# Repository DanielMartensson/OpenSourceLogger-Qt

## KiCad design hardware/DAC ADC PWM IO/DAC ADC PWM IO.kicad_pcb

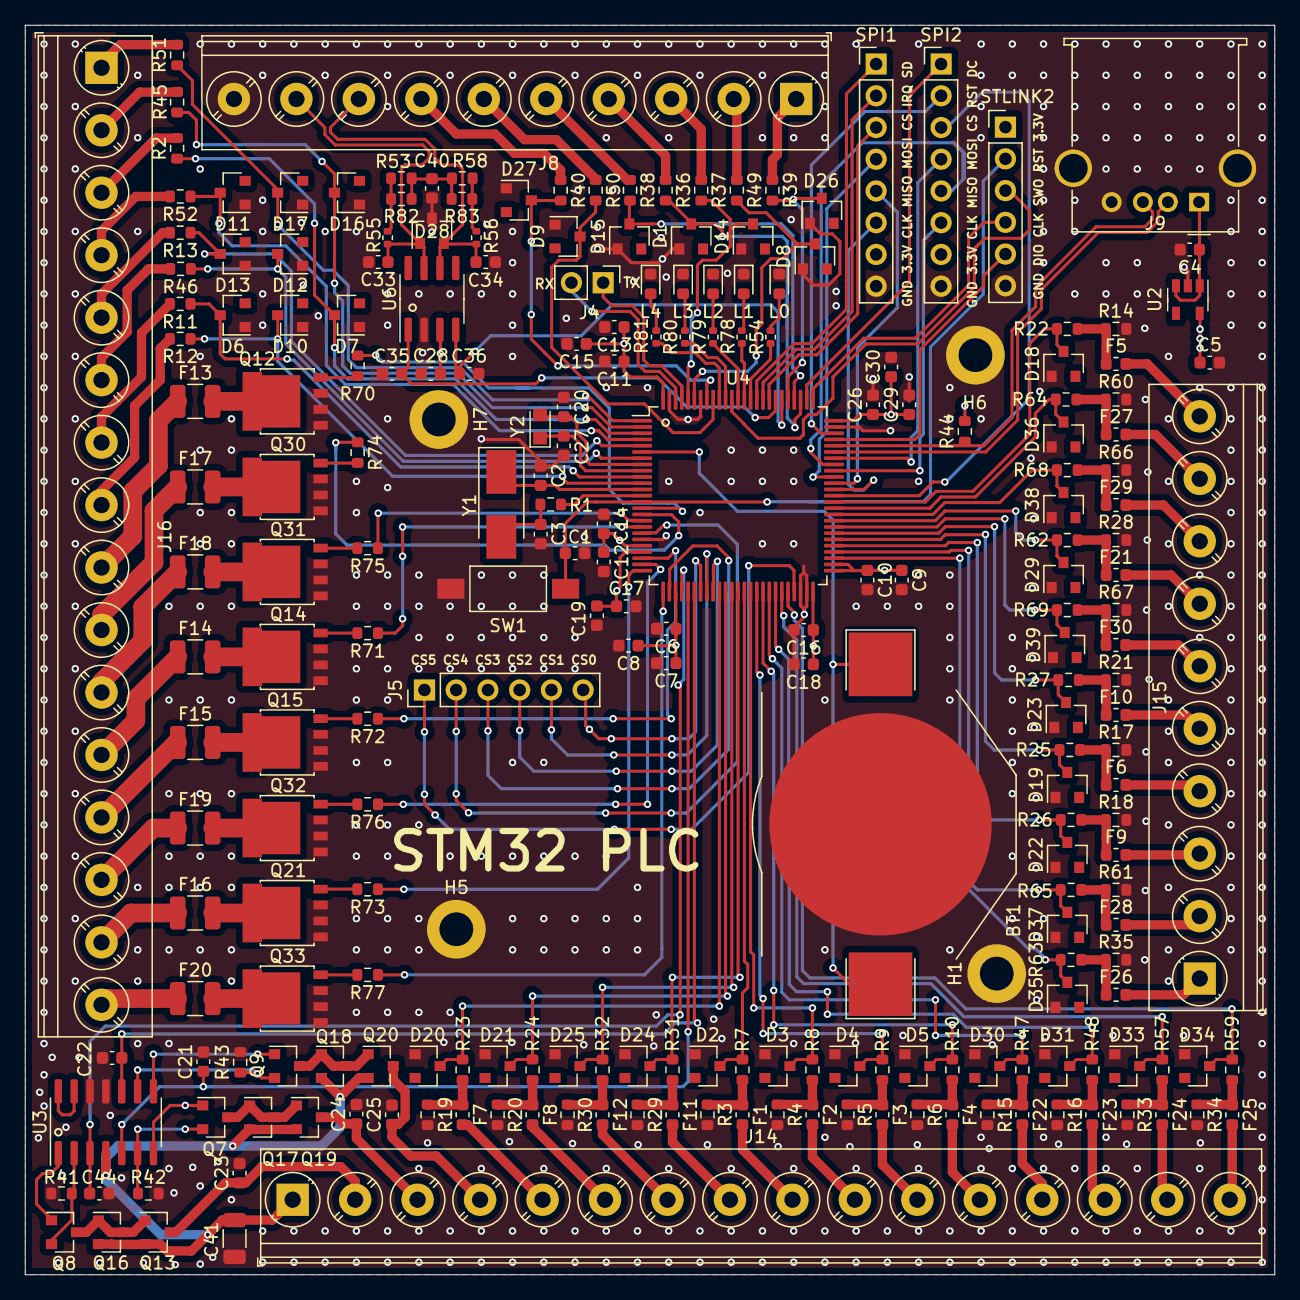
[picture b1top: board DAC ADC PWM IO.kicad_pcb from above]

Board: 4 copper layers, 100.0 x 100.0 mm, 232 parts (0 on the bottom side), 197 nets.

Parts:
BT1: Battery_Cell; BatteryHolder_Keystone_3002_1x2032
C1, C6, C7, C11, C13, C26, C29: 100nF; C_0603_1608Metric
C2, C3, C20, C27: 15pF; C_0603_1608Metric
C4, C5, C9, C14, C18, C19: 1uF; C_0603_1608Metric
C8, C15, C30: 4.7uF; C_0603_1608Metric
C10, C12, C16, C17, C21, C22, C23, C24, C25, C28, C33, C34, C35, C36, C40, C44: 10nF; C_0603_1608Metric
C41: 10uF; C_1206_3216Metric
D1, D2, D3, D4, D5, D6, D7, D8, D9, D10, D11, D12, D13, D14, D15, D16, D17, D18, D19, D20, D21, D22, D23, D24, D25, D26, D27, D29, D30, D31, D33, D34, D35, D36, D37, D38, D39: BZX84C3V6LT1G; D_SOT-23_ANK
D28: PESD5V0L2BT,215; SOT-23
F1, F2, F3, F4, F5, F6, F7, F8, F9, F10, F11, F12, F21, F22, F23, F24, F25, F26, F27, F28, F29, F30: Max 120mA; Fuse_0603_1608Metric
F13, F14, F15, F16, F17, F18, F19, F20: Max 2.2A; Fuse_1210_3225Metric
H1, H5, H6, H7: MountingHole_Pad; MountingHole_2.7mm_M2.5_DIN965_Pad
J4: Conn_01x02; PinHeader_1x02_P2.54mm_Vertical
J5: Chip Select; PinHeader_1x06_P2.54mm_Vertical
J8, J15: Screw_Terminal_01x10; TerminalBlock_Phoenix_PT-1,5-10-5.0-H_1x10_P5.00mm_Horizont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
J9: USB_A; USB_A_Molex_67643_Horizontal
J14, J16: Screw_Terminal_01x16; TerminalBlock_Phoenix_PT-1,5-16-5.0-H_1x16_P5.00mm_Horizont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
L0, L1, L2, L3, L4: LED; LED_0603_1608Metric
Q7, Q8, Q9: MMBT5551; SOT-23
Q12, Q14, Q15, Q21, Q30, Q31, Q32, Q33: PSMN025-80YL; LFPAK56
Q13, Q16, Q17, Q18, Q19, Q20: MMBT5401; SOT-23
R1, R44: 1.5k; R_0603_1608Metric
R2, R7, R8, R9, R10, R11, R12, R13, R22, R23, R24, R25, R26, R27, R31, R32, R36, R37, R38, R39, R40, R45, R46, R47, R48, R49, R50, R51, R52, R57, R59, R62, R63, R64, R65, R68, R69: 10k; R_0603_1608Metric
R3, R4, R5, R6, R14, R15, R16, R17, R18, R19, R20, R21, R28, R29, R30, R33, R34, R35, R41, R42, R43, R60, R61, R66, R67, R70, R71, R72, R73, R74, R75, R76, R77: 160; R_0603_1608Metric
R53, R58, R82, R83: 120; R_0603_1608Metric
R54, R78, R79, R80, R81: 220; R_0402_1005Metric
R55, R56: 0; R_0402_1005Metric
SPI1, SPI2: Conn_01x08; PinHeader_1x08_P2.54mm_Vertical
STLINK2: ST-Link V2 connetor; PinHeader_1x06_P2.54mm_Vertical
SW1: SW_Push; SW_SPST_FSMSM
U2: AP7365-33WG-7; SOT-23-5
U3: MC33079DT; SO-14_3.9x8.65mm_P1.27mm
U4: STM32F373VBTx; LQFP-100_14x14mm_P0.5mm
U6: TCAN332; SOIC-8_3.9x4.9mm_P1.27mm
Y1: HSE; Crystal_SMD_5032-2Pin_5.0x3.2mm_HandSoldering
Y2: 32.768 kHz; Crystal_SMD_2012-2Pin_2.0x1.2mm_HandSoldering

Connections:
+3V3: C5.1, C6.1, C7.1, C8.1, C9.1, C10.1, C11.1, C12.1, C13.1, C14.1, C15.1, C16.1, C17.1, C18.1, C19.1, C26.1, C28.1, C29.1, C30.1, R44.2, SPI1.7, SPI2.7, STLINK2.1, U2.5, U4.21, U4.22, U4.28, U4.50, U4.51, U4.52, U4.75, U4.100, U6.3
+5V: C4.1, J9.1, U2.1, U2.3
/CAN/CAN+: C33.2, D28.1, J8.9, R55.1, U6.7
/CAN/CAN-: C34.1, D28.2, J8.8, R56.2, U6.6
/DAC/AO0: C23.1, J14.2, Q13.3
/DAC/AO1: C24.1, J14.3, Q19.3
/DAC/AO2: C25.1, J14.4, Q20.3
/DAC/VDC: C41.1, J14.1, Q13.2, Q16.2, Q17.2, Q18.2, Q19.2, Q20.2, U3.4
/DSDADC/DAI0M: F28.2, J15.2
/DSDADC/DAI0P: F26.2, J15.1
/DSDADC/DAI1M: F6.2, J15.4
/DSDADC/DAI1P: F9.2, J15.3
/DSDADC/DAI2M: F30.2, J15.6
/DSDADC/DAI2P: F10.2, J15.5
/DSDADC/DAI3M: F29.2, J15.8
/DSDADC/DAI3P: F21.2, J15.7
/DSDADC/DAI4M: F5.2, J15.10
/DSDADC/DAI4P: F27.2, J15.9
/Digital/P0: F13.1, J16.9
/Digital/P1: F17.1, J16.10
/Digital/P2: F18.1, J16.11
/Digital/P3: F14.1, J16.12
/Digital/P4: F15.1, J16.13
/Digital/P5: F19.1, J16.14
/Digital/P6: F16.1, J16.15
/Digital/P7: F20.1, J16.16
/INPUT/DI0: J16.1, R51.2
/INPUT/DI1: J16.2, R45.1
/INPUT/DI2: J16.3, R2.2
/INPUT/DI3: J16.4, R52.2
/INPUT/DI4: J16.5, R13.2
/INPUT/DI5: J16.6, R46.2
/INPUT/DI6: J16.7, R11.2
/INPUT/DI7: J16.8, R12.1
/Pulse/E0+: J8.7, R40.1
/Pulse/E0-: J8.6, R50.1
/Pulse/E1+: J8.5, R38.1
/Pulse/E1-: J8.4, R36.1
/Pulse/FI0: J8.3, R37.1
/Pulse/FI1: J8.2, R49.1
/Pulse/FI2: J8.1, R39.1
/SDADC/AI0: F7.2, J14.5
/SDADC/AI1: F8.2, J14.6
/SDADC/AI2: F12.2, J14.7
/SDADC/AI3: F11.2, J14.8
/SDADC/AI4: F1.2, J14.9
/SDADC/AI5: F2.2, J14.10
/SDADC/AI6: F3.2, J14.11
/SDADC/AI7: F4.2, J14.12
/SDADC/AI8: F22.2, J14.13
/SDADC/AI9: F23.2, J14.14
/SDADC/AI10: F24.2, J14.15
/SDADC/AI11: F25.2, J14.16
GND: BT1.2, C1.1, C2.1, C3.1, C4.2, C5.2, C6.2, C7.2, C8.2, C9.2, C10.2, C11.2, C12.2, C13.2, C14.2, C15.2, C16.2, C17.2, C18.2, C19.2, C20.1, C21.2, C22.2, C23.2, C24.2, C25.2, C26.2, C27.1, C28.2, C29.2, C30.2, C33.1, C34.2, C35.1, C36.2, C40.2, C41.2, C44.2, D1.2, D2.2, D3.2, D4.2, D5.2, D6.2, D7.2, D8.2, D9.2, D10.2, D11.2, D12.2, D13.2, D14.2, D15.2, D16.2, D17.2, D18.2, D19.2, D20.2, D21.2, D22.2, D23.2, D24.2, D25.2, D26.2, D27.2, D28.3, D29.2, D30.2, D31.2, D33.2, D34.2, D35.2, D36.2, D37.2, D38.2, D39.2, H1.1, H5.1, H6.1, H7.1, J8.10, J9.4, J9.5, L0.1, L1.1, L2.1, L3.1, L4.1, Q12.1, Q12.2, Q12.3, Q14.1, Q14.2, Q14.3, Q15.1, Q15.2, Q15.3, Q21.1, Q21.2, Q21.3, Q30.1, Q30.2, Q30.3, Q31.1, Q31.2, Q31.3, Q32.1, Q32.2, Q32.3, Q33.1, Q33.2, Q33.3, R3.2, R4.2, R5.2, R6.2, R14.2, R15.2, R16.2, R17.2, R18.2, R19.2, R20.2, R21.2, R28.2, R29.2, R30.2, R33.2, R34.2, R35.2, R41.2, R42.2, R43.2, R60.2, R61.2, R66.2, R67.2, SPI1.8, SPI2.8, STLINK2.6, SW1.1, U2.2, U3.11, U3.12, U4.20, U4.48, U4.49, U4.74, U4.94, U4.99, U6.2
NRST: C1.2, STLINK2.2, SW1.2, U4.14
unnamed: BT1.1, U4.6
unnamed: C3.2, R1.1, Y1.2
unnamed: C40.1, R53.2, R58.1, R82.2, R83.1
unnamed: F1.1, R3.1, R7.1
unnamed: F2.1, R4.1, R8.1
unnamed: F3.1, R5.1, R9.1
unnamed: F4.1, R6.1, R10.1
unnamed: F5.1, R14.1, R22.1
unnamed: F6.1, R17.1, R25.1
unnamed: F7.1, R19.1, R23.1
unnamed: F8.1, R20.1, R24.1
unnamed: F9.1, R18.1, R26.1
unnamed: F10.1, R21.1, R27.1
unnamed: F11.1, R29.1, R31.1
unnamed: F12.1, R30.1, R32.1
unnamed: F13.2, Q12.5
unnamed: F14.2, Q14.5
unnamed: F15.2, Q15.5
unnamed: F16.2, Q21.5
unnamed: F17.2, Q30.5
unnamed: F18.2, Q31.5
unnamed: F19.2, Q32.5
unnamed: F20.2, Q33.5
unnamed: F21.1, R28.1, R62.1
unnamed: F22.1, R15.1, R47.1
unnamed: F23.1, R16.1, R48.1
unnamed: F24.1, R33.1, R57.1
unnamed: F25.1, R34.1, R59.1
unnamed: F26.1, R35.1, R63.1
unnamed: F27.1, R60.1, R64.1
unnamed: F28.1, R61.1, R65.1
unnamed: F29.1, R66.1, R68.1
unnamed: F30.1, R67.1, R69.1
unnamed: L0.2, R54.2
unnamed: L1.2, R78.2
unnamed: L2.2, R79.2
unnamed: L3.2, R80.2
unnamed: L4.2, R81.2
unnamed: Q7.1, U3.7
unnamed: Q7.2, R42.1, U3.6
unnamed: Q8.1, U3.1
unnamed: Q8.2, R41.1, U3.2
unnamed: Q9.1, U3.8
unnamed: Q9.2, R43.1, U3.9
unnamed: Q12.4, R70.2
unnamed: Q8.3, Q13.1, Q16.1, Q16.3
unnamed: Q14.4, R71.2
unnamed: Q15.4, R72.2
unnamed: Q7.3, Q17.1, Q17.3, Q19.1
unnamed: Q9.3, Q18.1, Q18.3, Q20.1
unnamed: Q21.4, R73.2
unnamed: Q30.4, R74.2
unnamed: Q31.4, R75.2
unnamed: Q32.4, R76.2
unnamed: Q33.4, R77.2
unnamed: R53.1, R55.2, R82.1
unnamed: R56.1, R58.2, R83.2
unnamed: U3.13, U3.14
PA0: R72.1, U4.23
PA1: R76.1, U4.24
PA2: R73.1, U4.25
PA3: R77.1, U4.26
PA4: C44.1, U3.3, U4.29
PA5: C21.1, U3.5, U4.30
PA6: C22.1, U3.10, U4.31
PA7: J5.6, U4.32
PA8: SPI2.6, U4.67
PA9: SPI2.5, U4.68
PA10: SPI2.4, U4.69
PA13: STLINK2.5, U4.72
PA14: STLINK2.4, U4.76
PA15: SPI2.1, U4.77
PB0: D20.1, R23.2, U4.35
PB1: D21.1, R24.2, U4.36
PB2: D25.1, R32.2, U4.37
PB3: STLINK2.3, U4.89
PB4: R80.1, U4.90
PB5: R81.1, U4.91
PB6: D9.1, R50.2, U4.92
PB7: D27.1, R40.2, U4.93
PB8: D8.1, R49.2, U4.95
PB9: D14.1, R37.2, U4.96
PB10: J5.1, U4.47
PB14: D35.1, R63.2, U4.53
PB15: D37.1, R65.2, U4.54
PC0: R70.1, U4.15
PC1: R74.1, U4.16
PC2: R75.1, U4.17
PC3: R71.1, U4.18
PC4: J5.5, U4.33
PC5: J5.4, U4.34
PC6: SPI2.3, U4.63
PC7: SPI1.6, U4.64
PC8: SPI1.5, U4.65
PC9: SPI1.4, U4.66
PC10: D1.1, R36.2, U4.78
PC11: D15.1, R38.2, U4.79
PC12: D26.1, R39.2, U4.80
PC13: D12.1, R46.1, U4.7
PC14: C20.2, U4.8, Y2.2
PC15: C27.2, U4.9, Y2.1
PD0: C36.1, U4.81, U6.4
PD1: C35.2, U4.82, U6.1
PD2: SPI1.3, U4.83
PD3: SPI1.2, U4.84
PD4: SPI1.1, U4.85
PD5: R54.1, U4.86
PD6: R78.1, U4.87
PD7: R79.1, U4.88
PD8: D22.1, R26.2, U4.55
PD9: D19.1, R25.2, U4.56
PD10: D23.1, R27.2, U4.57
PD11: D39.1, R69.2, U4.58
PD12: D29.1, R62.2, U4.59
PD13: D38.1, R68.2, U4.60
PD14: D36.1, R64.2, U4.61
PD15: D18.1, R22.2, U4.62
PE0: J4.1, U4.97
PE1: J4.2, U4.98
PE2: D17.1, R51.1, U4.1
PE3: D16.1, R45.2, U4.2
PE4: D7.1, R2.1, U4.3
PE5: D11.1, R52.1, U4.4
PE6: D13.1, R13.1, U4.5
PE7: D24.1, R31.2, U4.38
PE8: D2.1, R7.2, U4.39
PE9: D3.1, R8.2, U4.40
PE10: D4.1, R9.2, U4.41
PE11: D5.1, R10.2, U4.42
PE12: D30.1, R47.2, U4.43
PE13: D31.1, R48.2, U4.44
PE14: D33.1, R57.2, U4.45
PE15: D34.1, R59.2, U4.46
PF0: C2.2, U4.12, Y1.1
PF1: R1.2, U4.13
PF2: J5.2, U4.19
PF4: J5.3, U4.27
PF6: SPI2.2, U4.73
PF9: D6.1, R11.1, U4.10
PF10: D10.1, R12.2, U4.11
USB+: J9.3, R44.1, U4.71
USB-: J9.2, U4.70

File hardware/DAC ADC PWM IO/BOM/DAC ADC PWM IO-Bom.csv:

Comment,Designator,Footprint,LCSC
10nF,"C10,C12,C16,C17,C21,C22,C23,C24,C25,C28,C33,C34,C35,C36,C40,C44",Capacitor_SMD:C_0603_1608Metric,C57112
15pF,"C2,C3,C20,C27",Capacitor_SMD:C_0603_1608Metric,C1644
1uF,"C4,C5,C9,C14,C18,C19",Capacitor_SMD:C_0603_1608Metric,C15849
100nF,"C1,C6,C7,C11,C13,C26,C29",Capacitor_SMD:C_0603_1608Metric,C14663
4.7uF,"C8,C15,C30",Capacitor_SMD:C_0603_1608Metric,C19666
BZX84C3V6LT1G,"D1,D2,D3,D4,D5,D6,D7,D8,D9,D10,D11,D12,D13,D14,D15,D16,D17,D18,D19,D20,D21,D22,D23,D24,D25,D26,D27,D29,D30,D31,D33,D34,D35,D36,D37,D38,D39",Diode_SMD:D_SOT-23_ANK,C118564
Max 120mA,"F1,F2,F3,F4,F5,F6,F7,F8,F9,F10,F11,F12,F21,F22,F23,F24,F25,F26,F27,F28,F29,F30",Fuse:Fuse_0603_1608Metric,C426238
Max 2.2A,"F13,F14,F15,F16,F17,F18,F19,F20",Fuse:Fuse_1210_3225Metric,C20992
LED,"L0,L1,L2,L3,L4",LED_SMD:LED_0603_1608Metric,C2286
MMBT5401,"Q13,Q16,Q17,Q18,Q19,Q20",Package_TO_SOT_SMD:SOT-23,C8326
MMBT5551,"Q7,Q8,Q9",Package_TO_SOT_SMD:SOT-23,C2145
1.5k,"R1,R44",Resistor_SMD:R_0603_1608Metric,C22843
10k,"R2,R7,R8,R9,R10,R11,R12,R13,R22,R23,R24,R25,R26,R27,R31,R32,R36,R37,R38,R39,R40,R45,R46,R47,R48,R49,R50,R51,R52,R57,R59,R62,R63,R64,R65,R68,R69",Resistor_SMD:R_0603_1608Metric,C25804
220,"R54,R78,R79,R80,R81",Resistor_SMD:R_0402_1005Metric,C25091
120,"R53,R58,R82,R83",Resistor_SMD:R_0603_1608Metric,C22787
160,"R3,R4,R5,R6,R14,R15,R16,R17,R18,R19,R20,R21,R28,R29,R30,R33,R34,R35,R41,R42,R43,R60,R61,R66,R67,R70,R71,R72,R73,R74,R75,R76,R77",Resistor_SMD:R_0603_1608Metric,C22814

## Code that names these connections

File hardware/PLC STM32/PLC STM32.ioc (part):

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Mcu.Name=STM32F373V(8-B-C)Tx
Mcu.Package=LQFP100
Mcu.UserName=STM32F373VBTx
PA0.GPIOParameters=GPIO_Label
PA0.GPIO_Label=PWM4
PA0.Signal=S_TIM2_CH1_ETR
PA1.GPIOParameters=GPIO_Label
PA1.GPIO_Label=PWM5
PA1.Signal=S_TIM2_CH2
PA11.Mode=Device
PA11.Signal=USB_DM
PA12.Mode=Device
PA12.Signal=USB_DP
PA13.Mode=Trace_Asynchronous_SW
PA13.Signal=SYS_JTMS-SWDIO
PA14.Mode=Trace_Asynchronous_SW
PA14.Signal=SYS_JTCK-SWCLK
PA2.GPIOParameters=GPIO_Label
PA2.GPIO_Label=PWM6
PA2.Signal=S_TIM2_CH3
PA3.GPIOParameters=GPIO_Label
PA3.GPIO_Label=PWM7
PA3.Signal=S_TIM2_CH4
PA4.GPIOParameters=GPIO_Label
PA4.GPIO_Label=AO0
PA4.Signal=COMP_DAC11_group
PA5.GPIOParameters=GPIO_Label
PA5.GPIO_Label=AO1
PA5.Signal=COMP_DAC12_group
PA6.GPIOParameters=GPIO_Label
PA6.GPIO_Label=AO2
PA6.Signal=COMP_DAC21_group
PB0.GPIOParameters=GPIO_Label
PB0.GPIO_Label=AI0
PB0.Mode=IN6-Single-Ended zero reference
PB0.Signal=SDADC1_AIN6P
PB1.GPIOParameters=GPIO_Label
PB1.GPIO_Label=AI1
PB1.Mode=IN5-Single-Ended zero reference
PB1.Signal=SDADC1_AIN5P
PB14.GPIOParameters=GPIO_Label
PB14.GPIO_Label=DAI0P
PB14.Mode=IN8-Differential
PB14.Signal=SDADC3_AIN8P
PB15.GPIOParameters=GPIO_Label
PB15.GPIO_Label=DAI0M
PB15.Mode=IN8-Differential
PB15.Signal=SDADC3_AIN8M
PB2.GPIOParameters=GPIO_Label
PB2.GPIO_Label=AI2
PB2.Mode=IN4-Single-Ended zero reference
PB2.Signal=SDADC1_AIN4P
PB3.Mode=Trace_Asynchronous_SW
PB3.Signal=SYS_JTDO-TRACESWO
PB4.GPIOParameters=GPIO_Label
PB4.GPIO_Label=LED3
PB4.Signal=GPIO_Output
PB5.GPIOParameters=GPIO_Label
PB5.GPIO_Label=LED4
PB5.Signal=GPIO_Output
PB6.GPIOParameters=GPIO_Label
PB6.GPIO_Label=E0-
PB6.Signal=S_TIM4_CH1
PB7.GPIOParameters=GPIO_Label
PB7.GPIO_Label=E0+
PB7.Signal=S_TIM4_CH2
PB8.GPIOParameters=GPIO_Label
PB8.GPIO_Label=IC1
PB8.Signal=S_TIM16_CH1
PB9.GPIOParameters=GPIO_Label
PB9.GPIO_Label=IC0
PB9.Signal=S_TIM17_CH1
PC0.GPIOParameters=GPIO_Label
PC0.GPIO_Label=PWM0
PC0.Signal=S_TIM5_CH1_ETR
PC1.GPIOParameters=GPIO_Label
PC1.GPIO_Label=PWM1
PC1.Signal=S_TIM5_CH2
PC10.GPIOParameters=GPIO_Label
PC10.GPIO_Label=E1-
PC10.Signal=S_TIM19_CH1
PC11.GPIOParameters=GPIO_Label
PC11.GPIO_Label=E1+
PC11.Signal=S_TIM19_CH2
PC12.GPIOParameters=GPIO_PuPd,GPIO_Label
PC12.GPIO_Label=DI8
PC12.GPIO_PuPd=GPIO_PULLDOWN
PC12.Signal=GPIO_Input
PC13.GPIOParameters=GPIO_PuPd,GPIO_Label
PC13.GPIO_Label=DI5
PC13.GPIO_PuPd=GPIO_PULLDOWN
PC13.Signal=GPIO_Input
PC2.GPIOParameters=GPIO_Label
PC2.GPIO_Label=PWM2
PC2.Signal=S_TIM5_CH3
PC3.GPIOParameters=GPIO_Label
PC3.GPIO_Label=PWM3
PC3.Signal=S_TIM5_CH4
PD0.Mode=CAN_Activate
PD0.Signal=CAN_RX
PD1.Mode=CAN_Activate
PD1.Signal=CAN_TX
PD10.GPIOParameters=GPIO_Label
PD10.GPIO_Label=DAI2P
PD10.Mode=IN4-Differential
PD10.Signal=SDADC3_AIN4P
PD11.GPIOParameters=GPIO_Label
PD11.GPIO_Label=DAI2M
PD11.Mode=IN4-Differential
PD11.Signal=SDADC3_AIN4M
PD12.GPIOParameters=GPIO_Label
PD12.GPIO_Label=DAI3P
PD12.Mode=IN2-Differential
PD12.Signal=SDADC3_AIN2P
PD13.GPIOParameters=GPIO_Label
PD13.GPIO_Label=DAI3M
PD13.Mode=IN2-Differential
PD13.Signal=SDADC3_AIN2M
PD14.GPIOParameters=GPIO_Label
PD14.GPIO_Label=DAI4P
PD14.Mode=IN0-Differential
PD14.Signal=SDADC3_AIN0P
PD15.GPIOParameters=GPIO_Label
PD15.GPIO_Label=DAI4M
PD15.Mode=IN0-Differential
PD15.Signal=SDADC3_AIN0M
PD5.GPIOParameters=GPIO_Label
PD5.GPIO_Label=LED0
PD5.Signal=GPIO_Output
PD6.GPIOParameters=GPIO_Label
PD6.GPIO_Label=LED1
PD6.Signal=GPIO_Output
PD7.GPIOParameters=GPIO_Label
PD7.GPIO_Label=LED2
PD7.Signal=GPIO_Output
PD8.GPIOParameters=GPIO_Label
PD8.GPIO_Label=DAI1P
PD8.Mode=IN6-Differential
PD8.Signal=SDADC3_AIN6P
PD9.GPIOParameters=GPIO_Label
PD9.GPIO_Label=DAI1M
PD9.Mode=IN6-Differential
PD9.Signal=SDADC3_AIN6M
PE10.GPIOParameters=GPIO_Label
PE10.GPIO_Label=AI6
PE10.Mode=IN2-Single-Ended zero reference
PE10.Signal=SDADC1_AIN2P
PE11.GPIOParameters=GPIO_Label
PE11.GPIO_Label=AI7
PE11.Mode=IN1-Single-Ended zero reference
PE11.Signal=SDADC1_AIN1P
PE12.GPIOParameters=GPIO_Label
PE12.GPIO_Label=AI8
PE12.Mode=IN0-Single-Ended zero reference
PE12.Signal=SDADC1_AIN0P
PE13.GPIOParameters=GPIO_Label
PE13.GPIO_Label=AI9
PE13.Mode=IN2-Single-Ended zero reference
PE13.Signal=SDADC2_AIN2P
PE14.GPIOParameters=GPIO_Label
PE14.GPIO_Label=AI10
PE14.Mode=IN1-Single-Ended zero reference
PE14.Signal=SDADC2_AIN1P
PE15.GPIOParameters=GPIO_Label
PE15.GPIO_Label=AI11
PE15.Mode=IN0-Single-Ended zero reference
PE15.Signal=SDADC2_AIN0P
PE2.GPIOParameters=GPIO_PuPd,GPIO_Label
PE2.GPIO_Label=DI0
PE2.GPIO_PuPd=GPIO_PULLDOWN
PE2.Signal=GPIO_Input
PE3.GPIOParameters=GPIO_PuPd,GPIO_Label
PE3.GPIO_Label=DI1
PE3.GPIO_PuPd=GPIO_PULLDOWN
PE3.Signal=GPIO_Input
PE4.GPIOParameters=GPIO_PuPd,GPIO_Label
PE4.GPIO_Label=DI2
PE4.GPIO_PuPd=GPIO_PULLDOWN
PE4.Signal=GPIO_Input
PE5.GPIOParameters=GPIO_PuPd,GPIO_Label
PE5.GPIO_Label=DI3
PE5.GPIO_PuPd=GPIO_PULLDOWN
PE5.Signal=GPIO_Input
PE6.GPIOParameters=GPIO_PuPd,GPIO_Label
PE6.GPIO_Label=DI4
PE6.GPIO_PuPd=GPIO_PULLDOWN
PE6.Signal=GPIO_Input
PE7.GPIOParameters=GPIO_Label
PE7.GPIO_Label=AI3
PE7.Mode=IN3-Single-Ended zero reference
PE7.Signal=SDADC1_AIN3P
PE8.GPIOParameters=GPIO_Label
PE8.GPIO_Label=AI4
PE8.Mode=IN8-Single-Ended zero reference
PE8.Signal=SDADC1_AIN8P
PE9.GPIOParameters=GPIO_Label
PE9.GPIO_Label=AI5
PE9.Mode=IN7-Single-Ended zero reference
PE9.Signal=SDADC1_AIN7P
PF0-OSC_IN.Mode=HSE-External-Oscillator
PF0-OSC_IN.Signal=RCC_OSC_IN
PF1-OSC_OUT.Mode=HSE-External-Oscillator
PF1-OSC_OUT.Signal=RCC_OSC_OUT
PF10.GPIOParameters=GPIO_PuPd,GPIO_Label
PF10.GPIO_Label=DI7
PF10.GPIO_PuPd=GPIO_PULLDOWN
PF10.Signal=GPIO_Input
PF9.GPIOParameters=GPIO_PuPd,GPIO_Label
PF9.GPIO_Label=DI6
PF9.GPIO_PuPd=GPIO_PULLDOWN
PF9.Signal=GPIO_Input
RCC.HSEPLLFreq_Value=8000000
RCC.HSE_Timout=100
RCC.HSE_VALUE=8000000
RCC.SYSCLKFreq_VALUE=48000000
RCC.SYSCLKSource=RCC_SYSCLKSOURCE_PLLCLK
board=custom

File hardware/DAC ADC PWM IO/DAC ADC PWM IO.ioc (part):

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Mcu.Name=STM32F373C(8-B-C)Tx
Mcu.Package=LQFP48
Mcu.UserName=STM32F373CCTx
PA0.Mode=IN0
PA0.Signal=ADC1_IN0
PA1.Mode=IN1
PA1.Signal=ADC1_IN1
PA10.GPIOParameters=GPIO_Label
PA10.GPIO_Label=PWM 1
PA10.Signal=S_TIM2_CH4
PA11.Mode=Device
PA11.Signal=USB_DM
PA12.Mode=Device
PA12.Signal=USB_DP
PA13.Mode=Trace_Asynchronous_SW
PA13.Signal=SYS_JTMS-SWDIO
PA14.Mode=Trace_Asynchronous_SW
PA14.Signal=SYS_JTCK-SWCLK
PA15.GPIOParameters=GPIO_Label
PA15.GPIO_Label=PWM 3
PA15.Signal=S_TIM2_CH1_ETR
PA2.Mode=IN2
PA2.Signal=ADC1_IN2
PA3.Mode=IN3
PA3.Signal=ADC1_IN3
PA4.GPIOParameters=GPIO_Label
PA4.GPIO_Label=DAC 2
PA4.Signal=COMP_DAC11_group
PA5.GPIOParameters=GPIO_Label
PA5.GPIO_Label=DAC 1
PA5.Signal=COMP_DAC12_group
PA6.GPIOParameters=GPIO_Label
PA6.GPIO_Label=DAC 0
PA6.Signal=COMP_DAC21_group
PA8.GPIOParameters=GPIO_Label
PA8.GPIO_Label=FREQUENCY 2
PA8.Signal=S_TIM5_CH1_ETR
PA9.GPIOParameters=GPIO_Label
PA9.GPIO_Label=PWM 0
PA9.Signal=S_TIM2_CH3
PB0.GPIOParameters=GPIO_Label
PB0.GPIO_Label=SDA0_M
PB0.Mode=IN6-Differential
PB0.Signal=SDADC1_AIN6P
PB1.GPIOParameters=GPIO_Label
PB1.GPIO_Label=SDA0_P
PB1.Mode=IN6-Differential
PB1.Signal=SDADC1_AIN6M
PB14.GPIOParameters=GPIO_Label
PB14.GPIO_Label=SDADC 1
PB14.Mode=IN8-Single-Ended zero reference
PB14.Signal=SDADC3_AIN8P
PB15.GPIOParameters=GPIO_Label
PB15.GPIO_Label=SDADC 2
PB15.Mode=IN7-Single-Ended zero reference
PB15.Signal=SDADC3_AIN7P
PB2.GPIOParameters=GPIO_Label
PB2.GPIO_Label=SDADC 0
PB2.Mode=IN4-Single-Ended zero reference
PB2.Signal=SDADC1_AIN4P
PB3.Mode=Trace_Asynchronous_SW
PB3.Signal=SYS_JTDO-TRACESWO
PB4.GPIOParameters=GPIO_Label
PB4.GPIO_Label=E-
PB4.Signal=S_TIM3_CH1
PB5.GPIOParameters=GPIO_Label
PB5.GPIO_Label=E+
PB5.Signal=S_TIM3_CH2
PB6.GPIOParameters=GPIO_Label
PB6.GPIO_Label=PWM 4
PB6.Signal=S_TIM4_CH1
PB7.GPIOParameters=GPIO_Label
PB7.GPIO_Label=PWM 5
PB7.Signal=S_TIM4_CH2
PB8.GPIOParameters=GPIO_Label
PB8.GPIO_Label=FREQUENCY 1
PB8.Signal=S_TIM19_CH3
PB9.GPIOParameters=GPIO_Label
PB9.GPIO_Label=FREQUENCY 0
PB9.Signal=S_TIM19_CH4
PC13.GPIOParameters=GPIO_PuPd,GPIO_Label
PC13.GPIO_Label=INPUT 1
PC13.GPIO_PuPd=GPIO_PULLDOWN
PC13.Signal=GPIO_Input
PC14-OSC32_IN.GPIOParameters=GPIO_PuPd,GPIO_Label
PC14-OSC32_IN.GPIO_Label=INPUT 2
PC14-OSC32_IN.GPIO_PuPd=GPIO_PULLDOWN
PC14-OSC32_IN.Signal=GPIO_Input
PC15-OSC32_OUT.GPIOParameters=GPIO_PuPd,GPIO_Label
PC15-OSC32_OUT.GPIO_Label=INPUT 3
PC15-OSC32_OUT.GPIO_PuPd=GPIO_PULLDOWN
PC15-OSC32_OUT.Signal=GPIO_Input
PD8.GPIOParameters=GPIO_Label
PD8.GPIO_Label=SDADC 3
PD8.Mode=IN6-Single-Ended zero reference
PD8.Signal=SDADC3_AIN6P
PE8.GPIOParameters=GPIO_Label
PE8.GPIO_Label=SDA1_P
PE8.Mode=IN8-Differential
PE8.Signal=SDADC1_AIN8P
PE9.GPIOParameters=GPIO_Label
PE9.GPIO_Label=SDA1_M
PE9.Mode=IN8-Differential
PE9.Signal=SDADC1_AIN8M
PF0-OSC_IN.Mode=HSE-External-Oscillator
PF0-OSC_IN.Signal=RCC_OSC_IN
PF1-OSC_OUT.Mode=HSE-External-Oscillator
PF1-OSC_OUT.Signal=RCC_OSC_OUT
PF6.GPIOParameters=GPIO_Label
PF6.GPIO_Label=PWM 2
PF6.Signal=S_TIM4_CH4
PF7.GPIOParameters=GPIO_PuPd,GPIO_Label
PF7.GPIO_Label=INPUT 0
PF7.GPIO_PuPd=GPIO_PULLDOWN
PF7.Signal=GPIO_Input
RCC.HSEPLLFreq_Value=16000000
RCC.HSE_VALUE=16000000
RCC.SYSCLKFreq_VALUE=16000000
RCC.SYSCLKSource=RCC_SYSCLKSOURCE_HSE
board=custom

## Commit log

2021-07-04 Using QT framework in C++
2022-03-27 clean
2022-03-27 upload
2022-03-27 Test
2022-03-27 New update
2022-03-28 one more step
2022-05-28 Done!
2022-06-15 Found bug. PWM and DAC for USB - Fixed
